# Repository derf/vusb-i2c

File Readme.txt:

VUSB-based USB to I2C conversion board.

This setup assumes that you have a VUSB board with level conversion on D+ and D-
<http://vusb.wdfiles.com/local--files/hardware/level-conversion-with-zener.gif>,
use an ATTiny and have D+ is connected to INT0, D- to INT1,
SDA to PB6 and SCL to PB7. hardware pull-ups must be connected to SDA and SCL.

The commandline utilities are meant to be similar to the i2c-tools utilities.
vusb-i2cdetect can be used to scan a bus, while vusb-i2cget and vusb-i2cset
read/write data.

For instance, to set a MicroMoody's color to yellow:
> vusb-i2cset 17 0 0 255 255 0 0 1

Or, to read out the temperature from a TC74 thermal sensor:
> vusb-i2cget 77 1 0

The original VUSB readme follows:

-----

This is the README file for the PowerSwitch USB device.

PowerSwitch is an example application using Objective Development's
firmware-only USB driver for Atmel's AVR microcontrollers. It provides 8 bits
of parallel output intended to switch e.g. the power supply to electronic
devices. The PowerSwitch firmware is accompanied by a command line tool to
control the device.

Objective Development's USB driver is a firmware-only implementation of the
USB 1.1 standard (low speed device) on cheap single chip microcomputers of
Atmel's AVR series, such as the ATtiny2313 or even some of the small 8 pin
devices. It implements the standard to the point where useful applications
can be implemented. See the file "firmware/usbdrdv/usbdrv.h" for features
and limitations.

BUILDING AND INSTALLING

Both, the firmware and Unix command line tool are built with "make". You may
need to customize both makefiles.

Firmware:
The firmware for PowerSwitch requires avr-gcc and avr-libc (a C-library for
the AVR controller). Please read the instructions at
http://www.nongnu.org/avr-libc/user-manual/install_tools.html for how to
install the GNU toolchain (avr-gcc, assembler, linker etc.) and avr-libc.
If you are on Windows, download WinAVR (see http://winavr.sourceforge.net/).
For the Mac, we recommend AVR MacPack at http://www.obdev.at/avrmacpack/.

Once you have the GNU toolchain for AVR microcontrollers installed, you can
run "make" in the subdirectory "firmware". You may have to edit the Makefile
to use your preferred downloader with "make flash". Our current version is
built for avrdude with our AVR-Doper programmer.

Command Line Tool on Unix:
The command line tool requires libusb. Please download libusb from
http://libusb.sourceforge.net/ and install it before you compile. Change to
directory "commandline", check the settings in Makefile and edit them as
appropriate. Then type "make" to build the executable "powerSwitch" which can
be used to control the device.

Command Line Tool on Windows:
The command line tool uses libusb-win32. Please download libusb-win32 from
http://libusb-win32.sourceforge.net/. The small package
(libusb-win32-device-bin) should be sufficient. We need usb.h and libusb.a for
gcc (or your favorite compiler). Make sure that usb.h is in the include path
and libusb.a in the library search path (edit Makefile to achieve this).
Although it should be possible to compile the command line tool with any
compiler, we recommend that you use MSYS (to run make and other Unix tools)
and MinGW (for the gcc toolchain). Both can be downloaded for free from
http://www.mingw.org/.

If you want to develop Windows drivers without libusb-win32, see our
"Automator" project for an example.

WORKING WITH POWERSWITCH

Once you have compiled and flashed the firmware and compiled the command line
tool, you can move on to the fun part: Connect the device to a free USB port
of your computer or USB-hub. You should now be able to find the device in
any USB analyzer tool, e.g. SystemProfiler on Mac OS X. If you connect it
to a Windows PC, the "New Hardware" dialog will pop up and you can create
the appropriate info files with libusb-win32's inf-wizard.

The next step is to try the command line tool, e.g.:

    ./powerSwitch off 3

to turn off port 3 (all ports are on when the device has been cleared) or

    for i in 0 1 2 3 4 5 6 7; do ./powerSwitch off $i; done

in an sh or bash (not csh or tcsh) type shell to turn off all ports.

You can also switch a port on or off temporarily. Try

    ./powerSwitch on 0 2.5

to activate port 0 for two and a half seconds.

FILES IN THE DISTRIBUTION

Readme.txt ........ The file you are currently reading.
firmware .......... Source code of the controller firmware.
firmware/usbdrv ... USB driver -- See Readme.txt in this directory for info
commandline ....... Source code of the host software (needs libusb).
circuit ........... Circuit diagrams in PDF and EAGLE 4 format. A free version
                    of EAGLE is available for Linux, Mac OS X and Windows from
                    http://www.cadsoft.de/.
License.txt ....... Public license (GNU GPL2) for all contents of this project.
Changelog.txt ..... Logfile documenting changes in soft-, firm- and hardware.
Pitfalls.txt ...... List of possible pitfalls and solutions.

USING THE USB DRIVER FOR YOUR OWN PROJECTS

PowerSwitch is mainly an example, although it may be very useful by itself.
If you want to implement your own application based on our USB driver, see
the file "firmware/main.c" for the application specific part of the firmware.
PowerSwitch uses only the most basic driver interface. More information and a
full technical description of the driver's interface can be found in
"firmware/usbdrv/usbdrv.h". Please review the configuration options in
"firmware/usbdrv/usbconfig-prototype.h". PowerSwitch uses Objective
Development's free shared USB IDs by default. You may set your own USB IDs
in usbconfig.h. For more information about USB descriptors and IDs see the
document "USB in a Nutshell" available at
http://www.beyondlogic.org/usbnutshell/usb1.htm or the USB 1.1 standard
available at http://www.usb.org/. Don't forget to check the license agreement
for Objective Development's firmware-only USB driver!

ABOUT THE LICENSE

It is our intention to make our USB driver and this demo application
available to everyone. Moreover, we want to make a broad range of USB
projects and ideas for USB devices available to the general public. We
therefore want that all projects built with our USB driver are published
under an Open Source license. Our license for the USB driver and demo code is
the GNU General Public License Version 2 (GPL2). See the file "License.txt"
for details.

If you don't want to publish your source code under the GPL2, you can simply
pay money for AVR-USB. As an additional benefit you get USB PIDs for free,
licensed exclusively to you. See the file "CommercialLicense.txt" for details.

MORE INFORMATION

For more information about Objective Development's firmware-only USB driver
for Atmel's AVR microcontrollers please visit the URL

    http://www.obdev.at/products/avrusb/

A technical documentation of the driver's interface can be found in the file
"firmware/usbdrv/usbdrv.h".

(c) 2005, 2006, 2007 by OBJECTIVE DEVELOPMENT Software GmbH.
http://www.obdev.at/

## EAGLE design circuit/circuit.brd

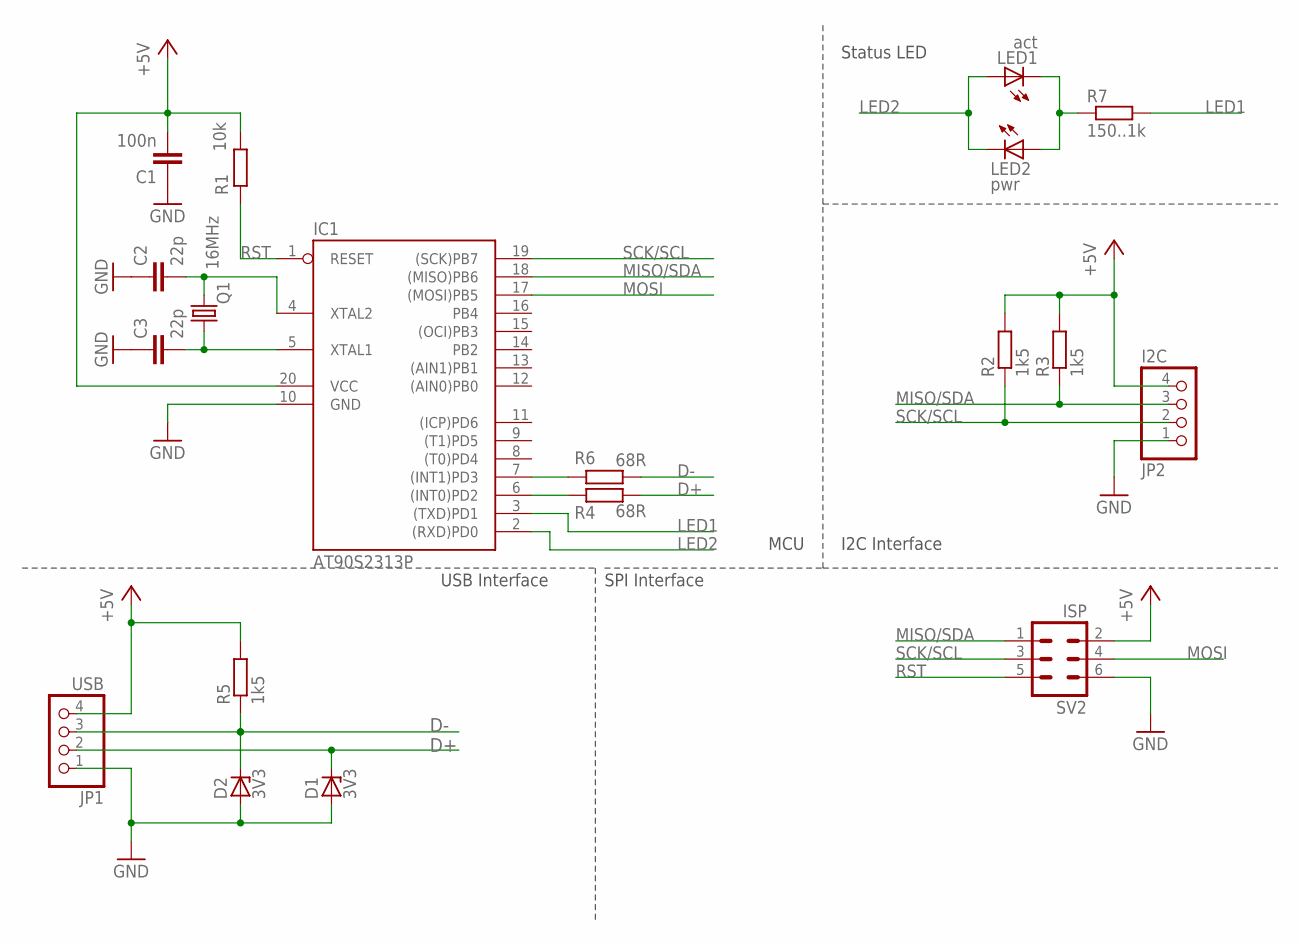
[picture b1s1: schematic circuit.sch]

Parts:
C1: 100n; C0805
C2, C3: 22p; C0805
D1, D2: 3V3; DO34Z7
IC1: AT90S2313P; DIL20
JP1: USB; 1X04
JP2: I2C; 1X04
LED1: act; LED3MM
LED2: pwr; LED3MM
Q1: 16MHz; HC49/S
R1: 10k; 0207/10
R2, R3, R5: 1k5; 0207/10
R4, R6: 68R; 0207/10
R7: 150..1k; 0207/10
SV2: ISP; ML6

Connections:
+5V: C1.2, IC1.20 (VCC), JP1.4, JP2.4, R1.2, R2.2, R3.2, R5.2, SV2.2
AVRD+: IC1.6 ((INT0)PD2), R4.2
AVRD-: IC1.7 ((INT1)PD3), R6.2
D+: D1.C, JP1.2, R4.1
D-: D2.C, JP1.3, R5.1, R6.1
EAE: LED1.K (C), LED2.A, R7.1
GND: C1.1, C2.1, C3.1, D1.A, D2.A, IC1.10 (GND), JP1.1, JP2.1, SV2.6
LED1: IC1.3 ((TXD)PD1), R7.2
LED2: IC1.2 ((RXD)PD0), LED1.A, LED2.K (C)
MISO/SDA: IC1.18 ((MISO)PB6), JP2.3, R3.1, SV2.1
MOSI: IC1.17 ((MOSI)PB5), SV2.4
unnamed: C3.2, IC1.5 (XTAL1), Q1.1
unnamed: C2.2, IC1.4 (XTAL2), Q1.2
RST: IC1.1 (RESET), R1.1, SV2.5
SCK/SCL: IC1.19 ((SCK)PB7), JP2.2, R2.1, SV2.3

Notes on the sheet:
USB Interface
MCU
I2C Interface
SPI Interface
Status LED

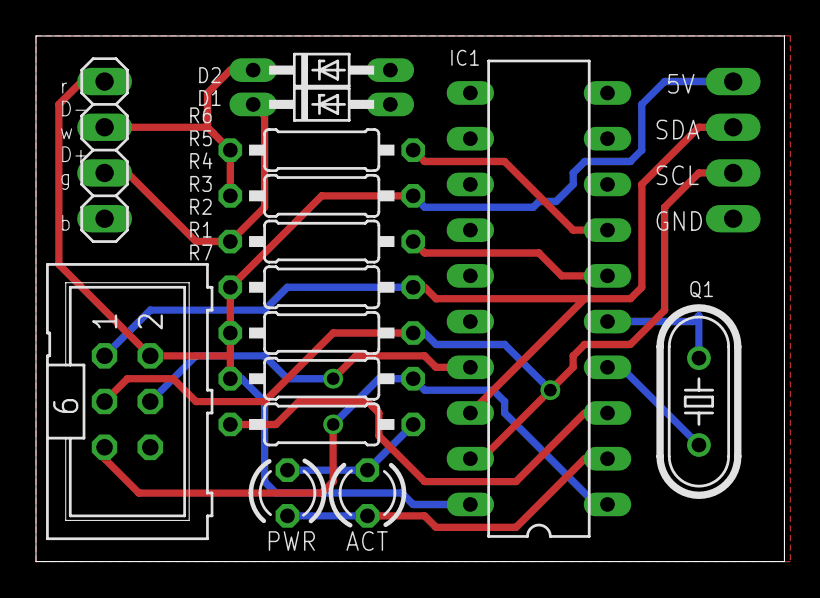
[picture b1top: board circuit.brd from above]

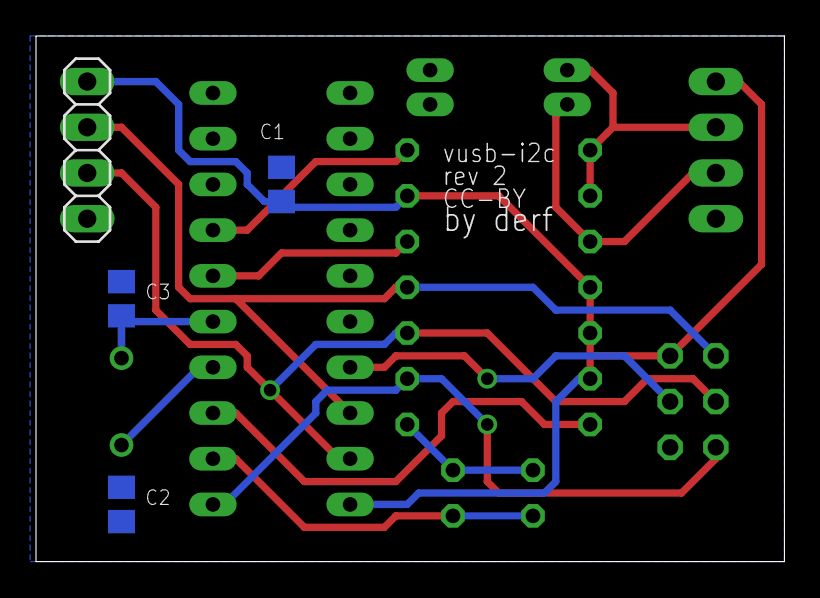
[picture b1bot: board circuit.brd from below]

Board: 2 copper layers, 41.6 x 29.2 mm, 19 parts (4 on the bottom side), 15 nets.

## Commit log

2013-05-17 rename powerSwitch to i2c (more accurate)
2013-05-20 makefile: add install target
2013-05-20 rename i2c to vusb-i2c
2013-06-07 leave space for ninth i2c (ack) bit
2013-06-29 firmware: fix initialization, disable software pull-ups, fix readout
2013-06-29 firmware: i2c is high by default
2013-06-29 commandline: verify bus state (not well-tested yet)
2013-06-30 now 100% i2c compliant. use "256" to read a byte
2013-07-16 commandline: use helper functions instead of defines for sda/scl control
2013-07-16 add i2cdetect
2013-07-28 move common code to i2c-util.c
2013-07-28 further abstraction
2013-07-28 add vusb-i2cwrite
2013-07-28 add vusb-i2cget
2013-07-28 rename i2cwrite to i2cset for i2c-tools compatibility
2013-07-28 start work on commandline documentation
2013-07-29 i2cget: read 16bit ints as well
2013-08-02 i2cdetect cleanup
2013-10-03 i2cget / i2cset: Accept hexadecimal input, document exit codes
2013-10-03 i2cdetect: Send START without prior STOP
2013-10-04 i2cset: use strtol for all conversions
2013-10-04 i2cget: Allow read commands of arbitrary length
2013-10-04 derease bus clock speed to ~10kHz
2013-10-04 add DS2482 Onewire READ ROM example script
2013-10-04 ds2482-100-readrom: use ABCDEF hex for chaosdorf foo compatibility
2013-10-04 update gitignore
2013-10-04 overdrive support
2013-10-04 readrom: add trailing newline
2013-10-04 add ds2482-100-searchrom (onewire SEARCH ROM)
2013-11-17 prepare to make sda/scl bits configurable
2013-11-17 add -c, -d to set sda/scl bit
2015-11-25 circuit: start work on board layout
2015-11-26 more baord layout improvements
2015-11-26 such layout, wow
2015-12-21 more layouting
2015-12-22 circuit: proper schematic
2015-12-22 circuit: Also, design rules...
2015-12-23 add first draft of SMD circuit
2015-12-23 further refinements
2015-12-23 add layout images
2015-12-24 ignore eagle backup files
2015-12-24 i2cget, i2cset: more error handling
2015-12-27 smd layout: add status LEDs, cause status LEDs are always good \o/
2015-12-29 smd rev 1 at board house
2015-12-29 tht circuit: preparing rev 2
2015-12-30 THT circuit: Adjust label placement
2015-12-30 circuits: normalize file names
2015-12-31 vusb-i2c-tht layout: Add a missing wire
2016-01-01 normalize firmware/Makefile (and always run make fuse_tiny2313)
2016-01-01 simplify USB protocol
2016-01-01 commandline: remove legacy 'vusb-i2c' program
2016-01-02 firmware: add support for power/activity LEDs
2016-01-02 i2cget, i2cset: properly terminate I2C connection in case of errors
2016-01-08 check software version between firmware and CLI
2016-01-08 use global defines for usb control commands
2016-01-09 move software I2C implementation to ATTiny
2016-01-10 firmware: clean up main.c, remove driver size test code
2016-01-30 firmware: Fix LED polarity mixup
2016-12-25 i2cget: support multi-byte reads
2016-12-25 add example script for lm75 temperature sensors
2016-12-25 Firmware: Always send proper stop conditions
2016-12-26 Firmware: Fix ACK in RX mode
2016-12-26 lm75 example: Add support for LM75BD (with 11-bit resolution)
2017-08-20 Send NAK after receiving last byte
2018-01-17 i2cget: Support reads without prior register address write
2018-01-17 Add example for reading out AM2320 temperature and humidity sensor
2021-04-08 add ssd1306 (I2C OLED display) examples
2021-04-11 examples/ssd1306: add support for 128x32 displays
2024-01-06 Update copyright
2024-01-06 add mailmap
2024-01-06 adjust ds2482-100 examples for vusb-i2cget multi-byte support
2024-01-06 Adjust Readme for vusb-i2cget multi-byte support

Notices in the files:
circuit/circuit.brd:
CC-BY
